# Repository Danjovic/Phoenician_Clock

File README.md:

# Phoenician_Clock
Digital clock with a LED bargraph display using Phoenician notation for individual digits.

## Introduction
Eevery digit of the (decimal) is displayed as a sequence of lit/unlit bars equivalent to the phoenician representation of digits 1 to 9. 

| Decimal | Phoenician |
|:---:|:---:|
| 1 | \| |
| 2 | \|\| |
| 3 | \|\|\| |
| 4 | \| \|\|\| |
| 5 | \|\| \|\|\| |
| 6 |  \|\|\|  \|\|\| |
| 7 | \| \|\|\| \|\|\| |
| 8 | \|\| \|\|\| \|\|\| |
| 9 | \|\|\| \|\|\| \|\|\| |

#### Dealing wiht the zero

The Phoenicians do not have a zero but it can be displayed as no segment lit. It is necessary, though, to justify the digits to the left or to the right to differentiate 10 from 01

| minute | Display |
|:---:|:---:|
| 05 | --------------\|\| \|\|\| |
| 50 | \|\| \|\|\|-------------- |

### How many bars ?
The biggest number to be displayed is 59. It takes at least 19 bars, being 6 for the digit 5 and 11 bars for the digit 9 plus two bars of spacing.
  
\|\|-\|\|\|--\|\|\|-\|\|\|-\|\|\|   

A couple of 10 segment Bargraph modules will be enough to represent the time.

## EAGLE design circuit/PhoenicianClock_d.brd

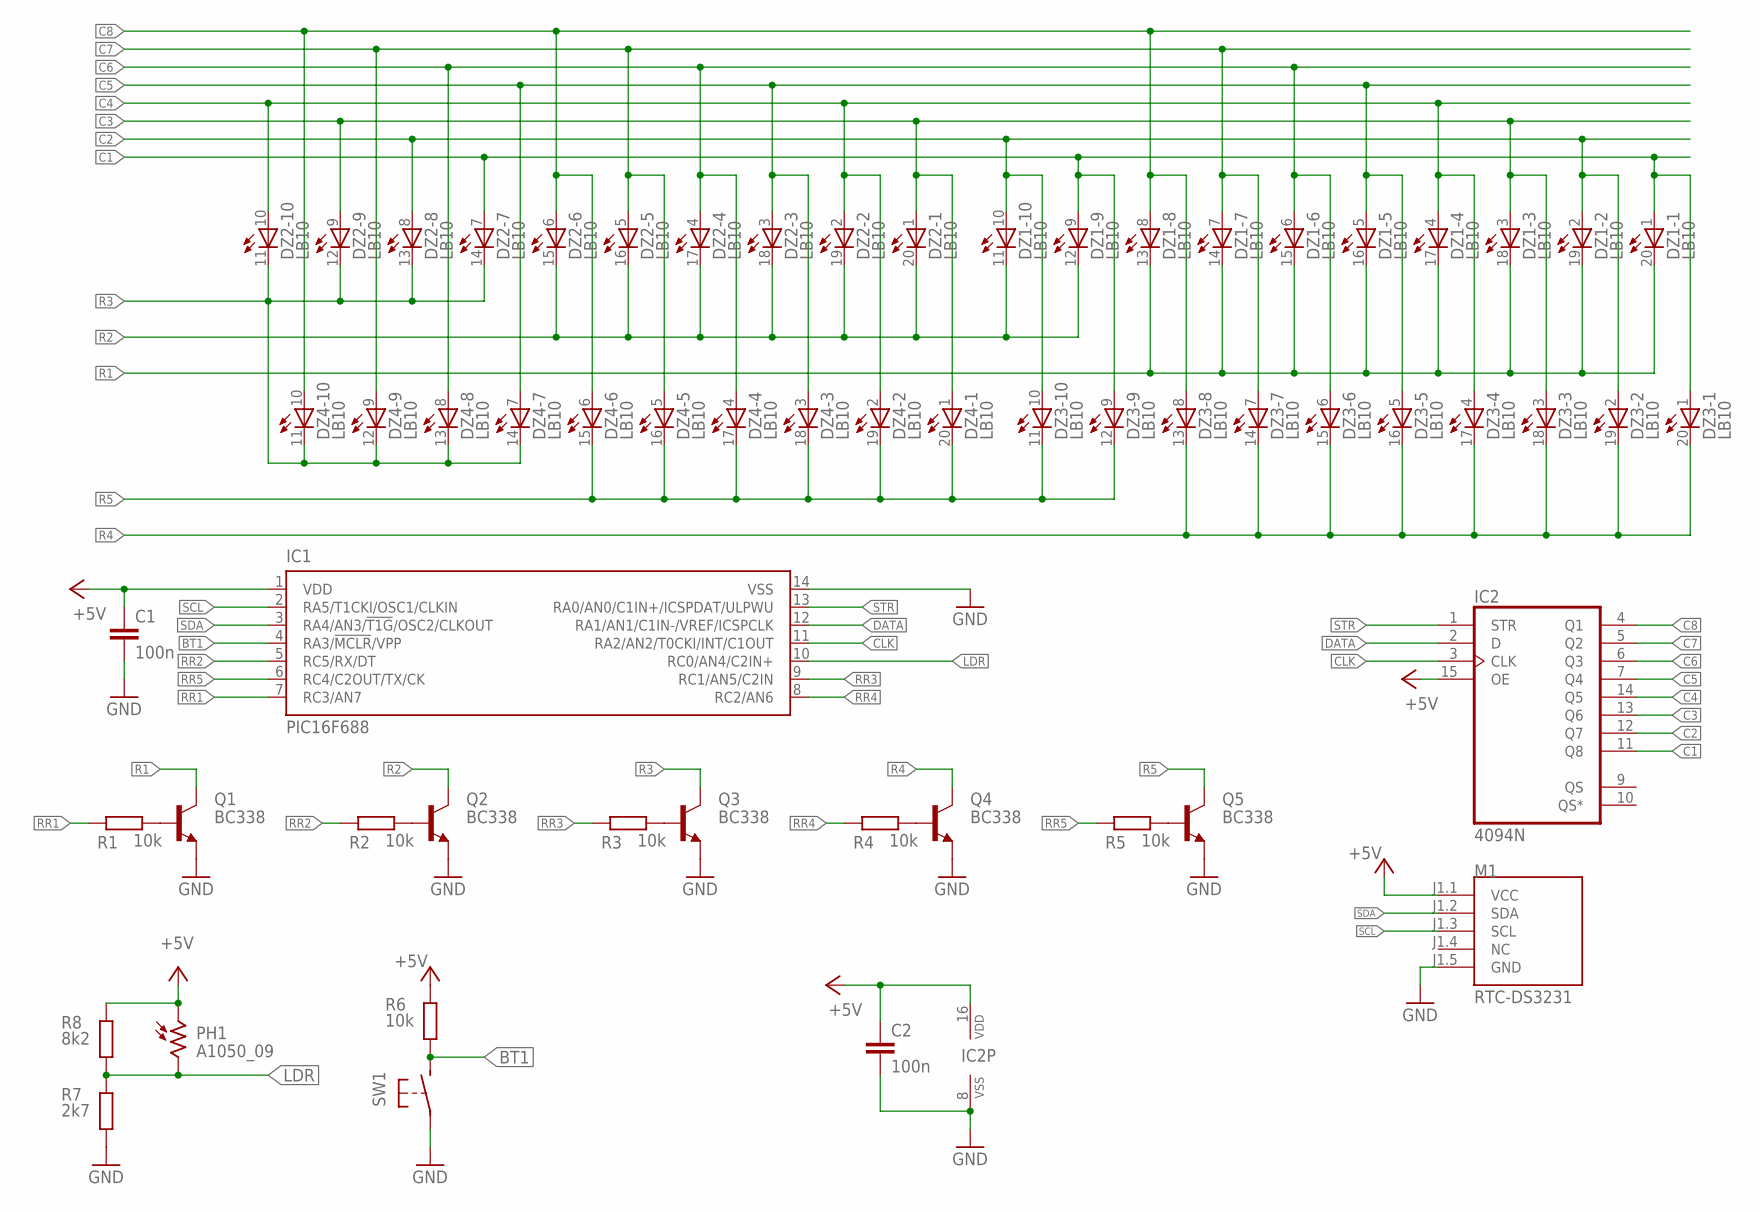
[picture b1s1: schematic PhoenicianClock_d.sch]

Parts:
C1, C2: 100n; C050-024X044
DZ1, DZ2, DZ3, DZ4: LB10
IC1: PIC16F688; DIL14
IC2: 4094N; DIL16
M1: RTC-DS3231; RTC-DS3231_SMALL
PH1: A1050_09; T0-46-A10XX
Q1, Q2, Q3, Q4, Q5: BC338; TO92-EBC
R1, R2, R3, R4, R5, R6: 10k; 0204/5
R7: 2k7; 0204/5
R8: 8k2; 0204/5
SW1: MINISPDT; 2PST_MINI

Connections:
+5V: C1.1, C2.1, IC1.1 (VDD), IC2.15 (OE), IC2.16 (VDD), M1.J1.1 (VCC), PH1.1, R6.2, R8.2
BT1: IC1.4 (RA3/!MCLR!/VPP), R6.1, SW1.P$2 (S)
C1: DZ1.1 (A), DZ1.9 (A), DZ2.7 (A), DZ3.1 (A), DZ3.9 (A), IC2.11 (Q8)
C2: DZ1.2 (A), DZ1.10 (A), DZ2.8 (A), DZ3.2 (A), DZ3.10 (A), IC2.12 (Q7)
C3: DZ1.3 (A), DZ2.1 (A), DZ2.9 (A), DZ3.3 (A), DZ4.1 (A), IC2.13 (Q6)
C4: DZ1.4 (A), DZ2.2 (A), DZ2.10 (A), DZ3.4 (A), DZ4.2 (A), IC2.14 (Q5)
C5: DZ1.5 (A), DZ2.3 (A), DZ3.5 (A), DZ4.3 (A), DZ4.7 (A), IC2.7 (Q4)
C6: DZ1.6 (A), DZ2.4 (A), DZ3.6 (A), DZ4.4 (A), DZ4.8 (A), IC2.6 (Q3)
C7: DZ1.7 (A), DZ2.5 (A), DZ3.7 (A), DZ4.5 (A), DZ4.9 (A), IC2.5 (Q2)
C8: DZ1.8 (A), DZ2.6 (A), DZ3.8 (A), DZ4.6 (A), DZ4.10 (A), IC2.4 (Q1)
CLK: IC1.11 (RA2/AN2/T0CKI/INT/C1OUT), IC2.3 (CLK)
DATA: IC1.12 (RA1/AN1/C1IN-/VREF/ICSPCLK), IC2.2 (D)
GND: C1.2, C2.2, IC1.14 (VSS), IC2.8 (VSS), M1.J1.5 (GND), Q1.E, Q2.E, Q3.E, Q4.E, Q5.E, R7.1, SW1.P$1
LDR: IC1.10 (RC0/AN4/C2IN+), PH1.2, R7.2, R8.1
unnamed: Q1.B, R1.2
unnamed: Q2.B, R2.2
unnamed: Q3.B, R3.2
unnamed: Q4.B, R4.2
unnamed: Q5.B, R5.2
R1: DZ1.13 (C), DZ1.14 (C), DZ1.15 (C), DZ1.16 (C), DZ1.17 (C), DZ1.18 (C), DZ1.19 (C), DZ1.20 (C), Q1.C
R2: DZ1.11 (C), DZ1.12 (C), DZ2.15 (C), DZ2.16 (C), DZ2.17 (C), DZ2.18 (C), DZ2.19 (C), DZ2.20 (C), Q2.C
R3: DZ2.11 (C), DZ2.12 (C), DZ2.13 (C), DZ2.14 (C), DZ4.11 (C), DZ4.12 (C), DZ4.13 (C), DZ4.14 (C), Q3.C
R4: DZ3.13 (C), DZ3.14 (C), DZ3.15 (C), DZ3.16 (C), DZ3.17 (C), DZ3.18 (C), DZ3.19 (C), DZ3.20 (C), Q4.C
R5: DZ3.11 (C), DZ3.12 (C), DZ4.15 (C), DZ4.16 (C), DZ4.17 (C), DZ4.18 (C), DZ4.19 (C), DZ4.20 (C), Q5.C
RR1: IC1.7 (RC3/AN7), R1.1
RR2: IC1.5 (RC5/RX/DT), R2.1
RR3: IC1.9 (RC1/AN5/C2IN), R3.1
RR4: IC1.8 (RC2/AN6), R4.1
RR5: IC1.6 (RC4/C2OUT/TX/CK), R5.1
SCL: IC1.2 (RA5/T1CKI/OSC1/CLKIN), M1.J1.3 (SCL)
SDA: IC1.3 (RA4/AN3/!T1G!/OSC2/CLKOUT), M1.J1.2 (SDA)
STR: IC1.13 (RA0/AN0/C1IN+/ICSPDAT/ULPWU), IC2.1 (STR)

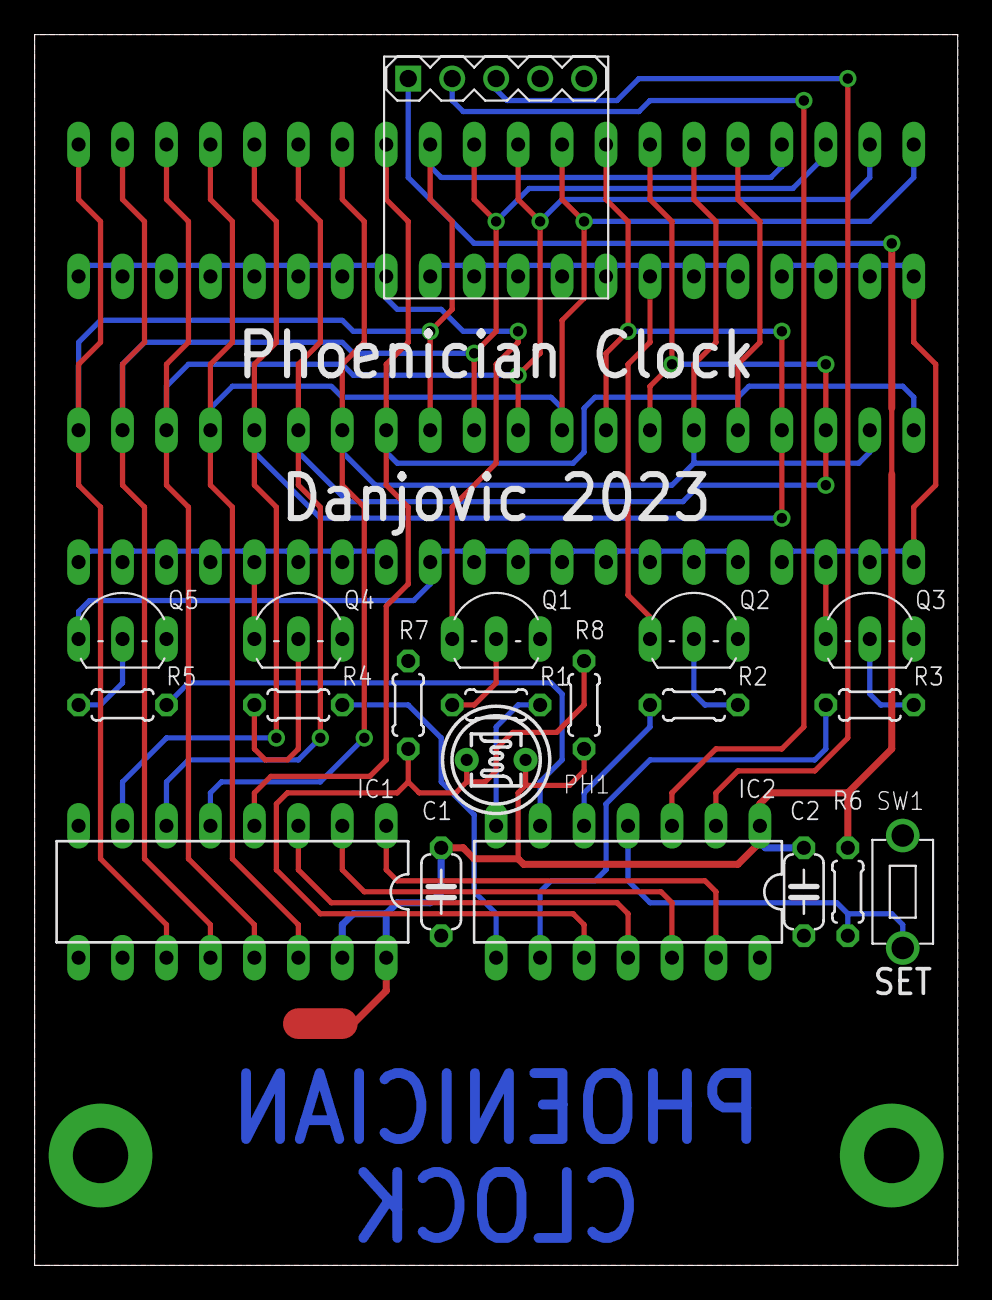
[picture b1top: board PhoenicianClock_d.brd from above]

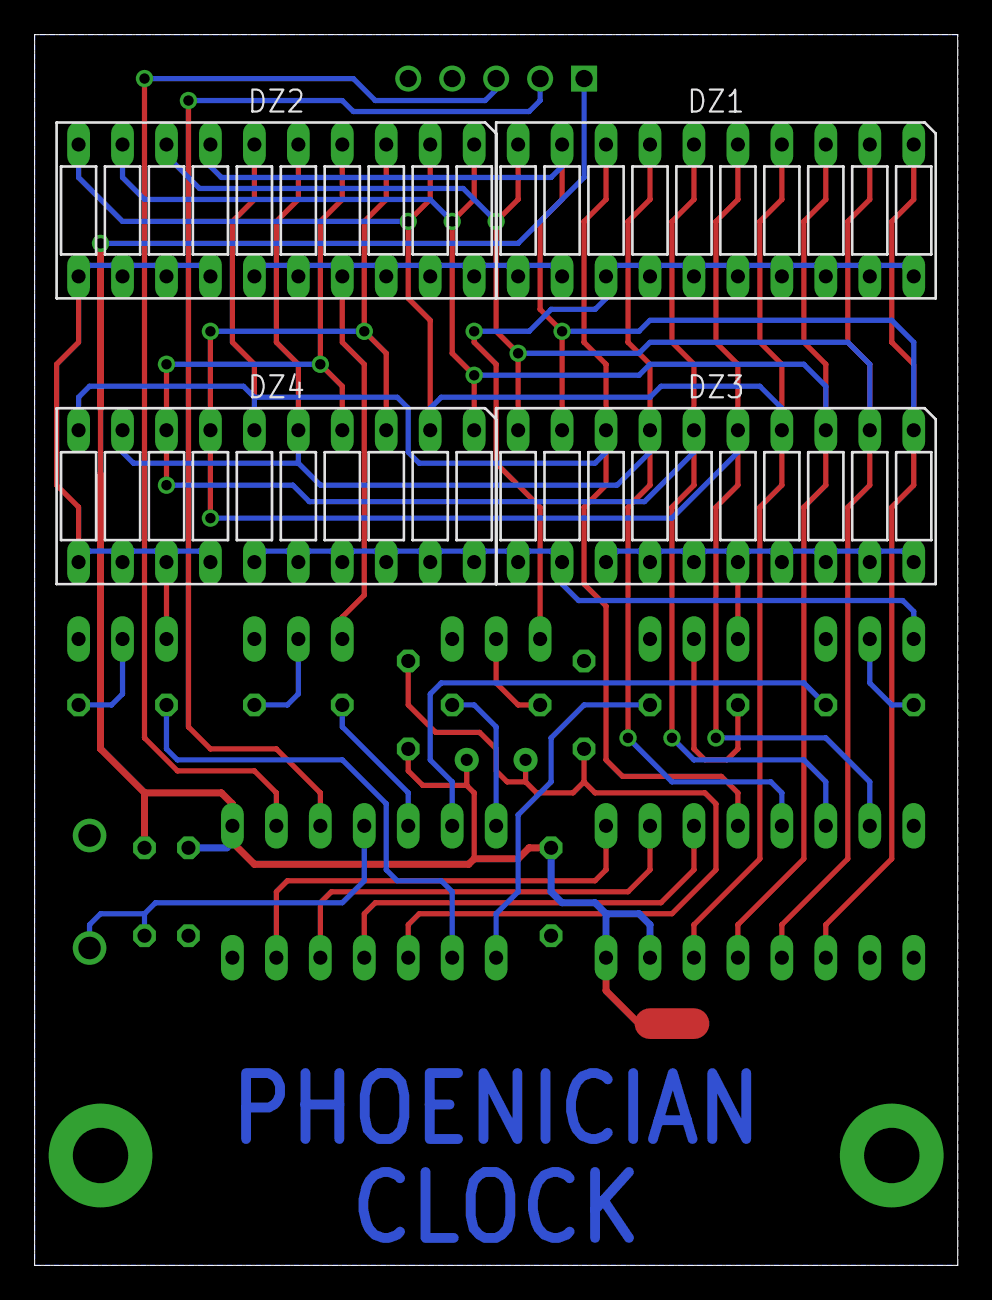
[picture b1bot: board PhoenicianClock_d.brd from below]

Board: 2 copper layers, 53.3 x 71.1 mm, 24 parts (4 on the bottom side), 32 nets.

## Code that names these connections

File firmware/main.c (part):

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#define ON  1

// I2C Stuff
#define SDA  RA4
#define SCL  RA5
#define sendACK     true
#define sendNACK    false
#define RTC_ADDRESS 0x68
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#define DIR_SCL TRISA5

// Shift Register Stuff
#define STROBE RA0
#define DOUT   RA1
#define CLOCK  RA2

// Display Columns
#define RR1 RC3
#define RR2 RC5
#define RR3 RC1
#define RR4 RC2
#define RR5 RC4

// Buttons Stuff
#define btnSET RA3
#define th_SHORT_PRESS 3    // time thresholds
#define th_LONG_PRESS 25   // in units of 20ms

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
   
      
   TRISC=0b00000001; // RC0 as input (LDR), other pins as outputs (rows) 
   PORTC=0b00000000; // all digits unactive
    
   TRISA=0b11111000; // RA0,RA1,RA2 as outputs, other pins as inputs 
   PORTA=0b00000000; // All low   
   WPUA4 = 1;  // pullups on i2c signals
   WPUA5 = 1;
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
   // Initialize A/D converter
   ANSEL = (1<<4); // Configure analog/digital I/O (ANSEL)
   ADCON0 = 0b00010000; // CHS[2..0] = 100 -> Channel AN4 (@pin RC0)
   ADCON1 = 0b01110000;	 //  ADCS1 [2..0] = x11 -> FRC Internal 500KHz oscillator
   ADON = 1;
   GO_NOT_DONE = 1;   // Set GO/DONE bit to start conversions
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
